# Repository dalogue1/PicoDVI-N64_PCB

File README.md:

# PicoDVI-N64_PCB
Project to create a PCB to connect the [PicoDVI-N64](https://github.com/kbeckmann/PicoDVI-N64) project by Konrad Beckmann.

The current status of the board I have made is as follows.  I have created and checked the board many times.  I have ordered it and will be testing it when it arrives. I will post installation photos and instructions when possible.

It includes everything needed in a PCB that can be ordered from jlcpcb for $2 for five boards.  The remaining parts in the BOM from Mouser will be about $5 plus shipping.  The RPi Pico or Pico-W is a separate cost.  

## The features include: 

- Fits securely in the N64 using a no-cut 3D printed adapter from the [n64adv2_pcb](https://github.com/borti4938/n64adv2_pcb) open-source project by Peter Bartmann.  
- USB port works without disconnecting power from the N64. (useful for software updates)
- Works with the full or part flex cables from the n64adv2_pcb project
- Works with a $12 flex cable for N64Digital from [HISPEEDIDO](https://www.aliexpress.us/item/3256805571419579.html?spm=5261.ProductManageOnline.0.0.33212ddbdJ53Tz&gatewayAdapt=glo2usa4itemAdapt) on AliExpress.
- Both flex cable connections use FFC sockets  (Important note: the flex cable connectors need to have top contacts not bottom.)
- Connects PIF Control and Reset signals to gpio pins 20 and 21
  - directly for the n64adv2 flex cable
  - via 47 ohm in-line resistors for the HISPEEDIDO flex cable
- Connects the HDMI CEC signal to gpio pin 22 via a 0k resistor
- To connect HDMI, the PCB implements the equivalent of the [Pico-DVI-Sock](https://github.com/Wren6991/Pico-DVI-Sock) by Luke Wren.
- Passes 5V power to the HDMI port via a 0k resistor
- Adds 2.2k pull-up resistors to 5V for HDMI SCL and SDA signals
- All resistors and resistor networks are large enough for hand-soldering by DIYers

## Additional information: 

This project is created in KiCad 6.0.11 and the project files are included. The zip for the Gerber Files is provided as well.

After some initial testing, it appears as if the termination resistors on the part flex or on the HISPEEDIDO flex need to be replaced with 0 ohm resistors.  More investigation will be done to determine why because without the resistors the n64adv2 flex would be incompatible with the N64 RGB Mod.  Possibly 33 ohm resistor packs may work.  Further testing will be made to determine what are the best resistor packs to put on the flex cable.

Modifications have been made to the PCB to attempt to allow it to fit in varying N64 versions without cutting.  If anyone has difficulty with the PCB not fitting please let me know in the PicoDVI-N64 Discord chat or in a PM to @dalogue in Discord.

Test fit of an early version of the board.  The new version of the board has much smaller overlap to work with other versions of the N64 motherboard with wider screw mounts.  Also, the flex cable needed additional space.  The board should be connected to the case with a piece of the 3M double stick tape. (same method used by the HISPEEDIDO adapter)

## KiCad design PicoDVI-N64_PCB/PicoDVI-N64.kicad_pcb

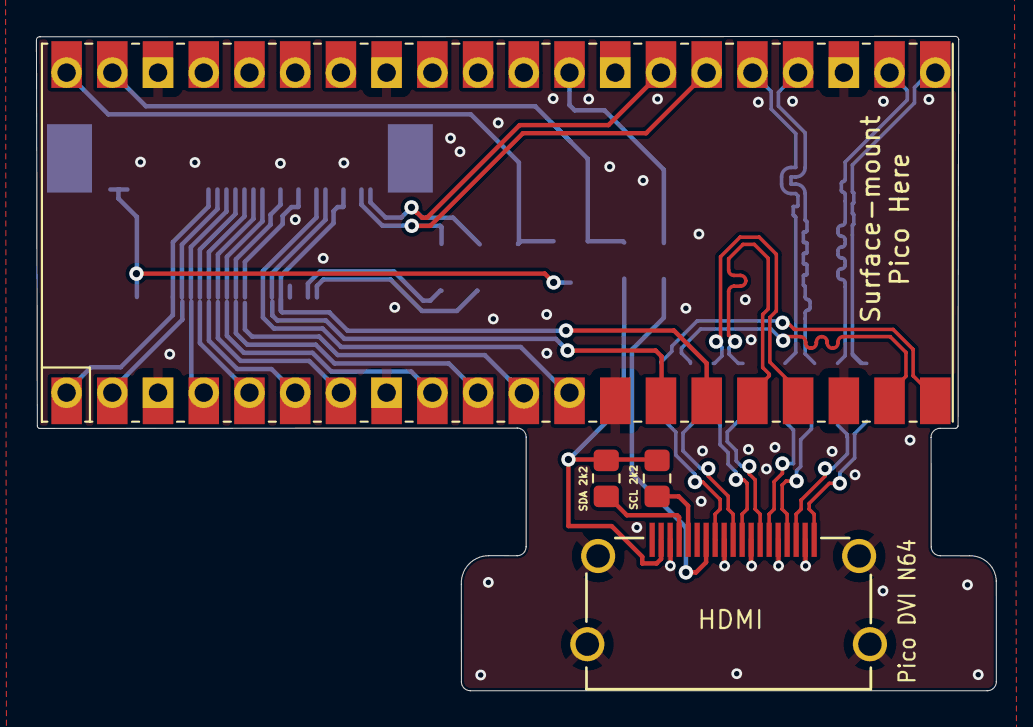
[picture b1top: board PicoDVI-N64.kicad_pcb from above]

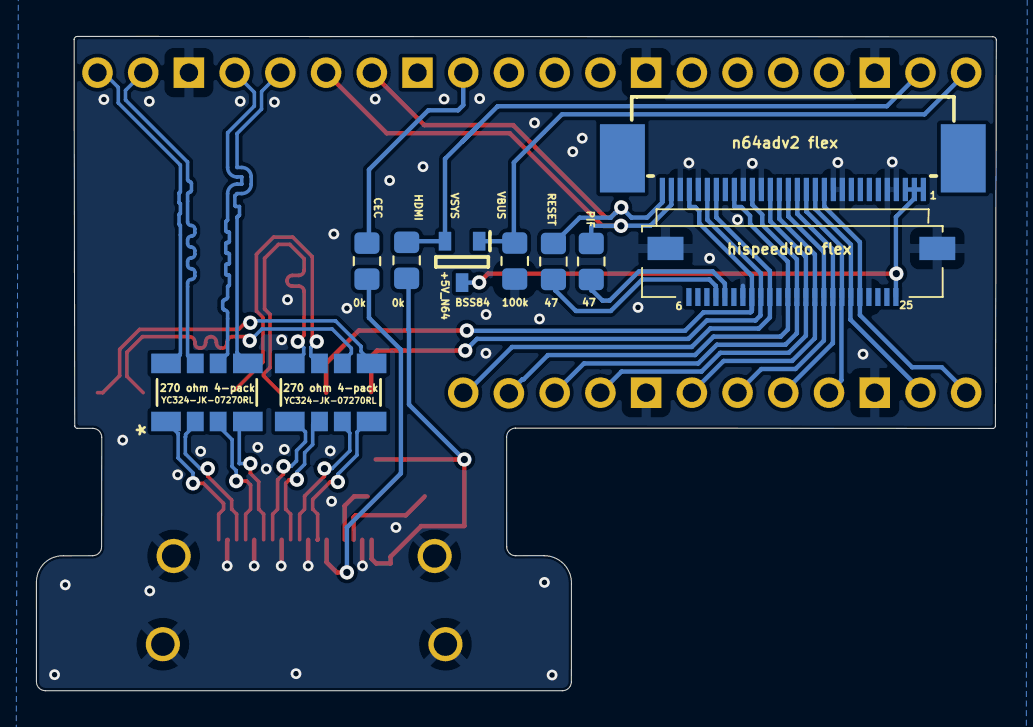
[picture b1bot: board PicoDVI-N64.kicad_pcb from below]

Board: 2 copper layers, 53.3 x 36.3 mm, 4 parts (3 on the bottom side), 14 nets.

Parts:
J4: NOT_HDMI_A; HDMI-SS-53000
J**: 5051102091
Q**: SOT95P240X120-3N
X1: 3-1734592-0; FH12-30S-0.5SH

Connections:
+5V_N64: J**.1, Q**.3, X1.1, X1.2, X1.3
AUDIO_BCLK: J**.17, X1.27
AUDIO_LRCK: J**.15, X1.24
AUDIO_SDAT: J**.16, X1.25
GND: J4.2 (D2S), J4.5 (D1S), J4.8 (D0S), J4.11 (CKS), J4.17 (GND), J4.SH, J**.4, J**.14, J**.18, X1.4, X1.5, X1.10, X1.11, X1.19, X1.21, X1.26, X1.28
VIDEO_CLK: J**.13, X1.22
VIDEO_D0: J**.5, X1.12
VIDEO_D1: J**.6, X1.13
VIDEO_D2: J**.7, X1.14
VIDEO_D3: J**.8, X1.15
VIDEO_D4: J**.9, X1.16
VIDEO_D5: J**.10, X1.17
VIDEO_D6: J**.11, X1.18
VIDEO_SYNC: J**.12, X1.20
